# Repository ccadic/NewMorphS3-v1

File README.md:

# NewMorphS3-v1
SMall S3 DEV Board with PSP Joystick
@sulfuroid

Hi all this is the NEW MorphS3 with ESP32S3 wroom chip.
You get a battery charger on board - Most of the GPIOS available
You have a 176x320 IPS ST7789 Display (compatible with TFT_eSPI 
There is a small PSP1000 joystick to help you make games
USB connection is a SMD USB C

Heve fun.

BOM and links to the components: https://github.com/ccadic/NewMorphS3-v1/blob/main/NewmorphS3-BOM.xlsx

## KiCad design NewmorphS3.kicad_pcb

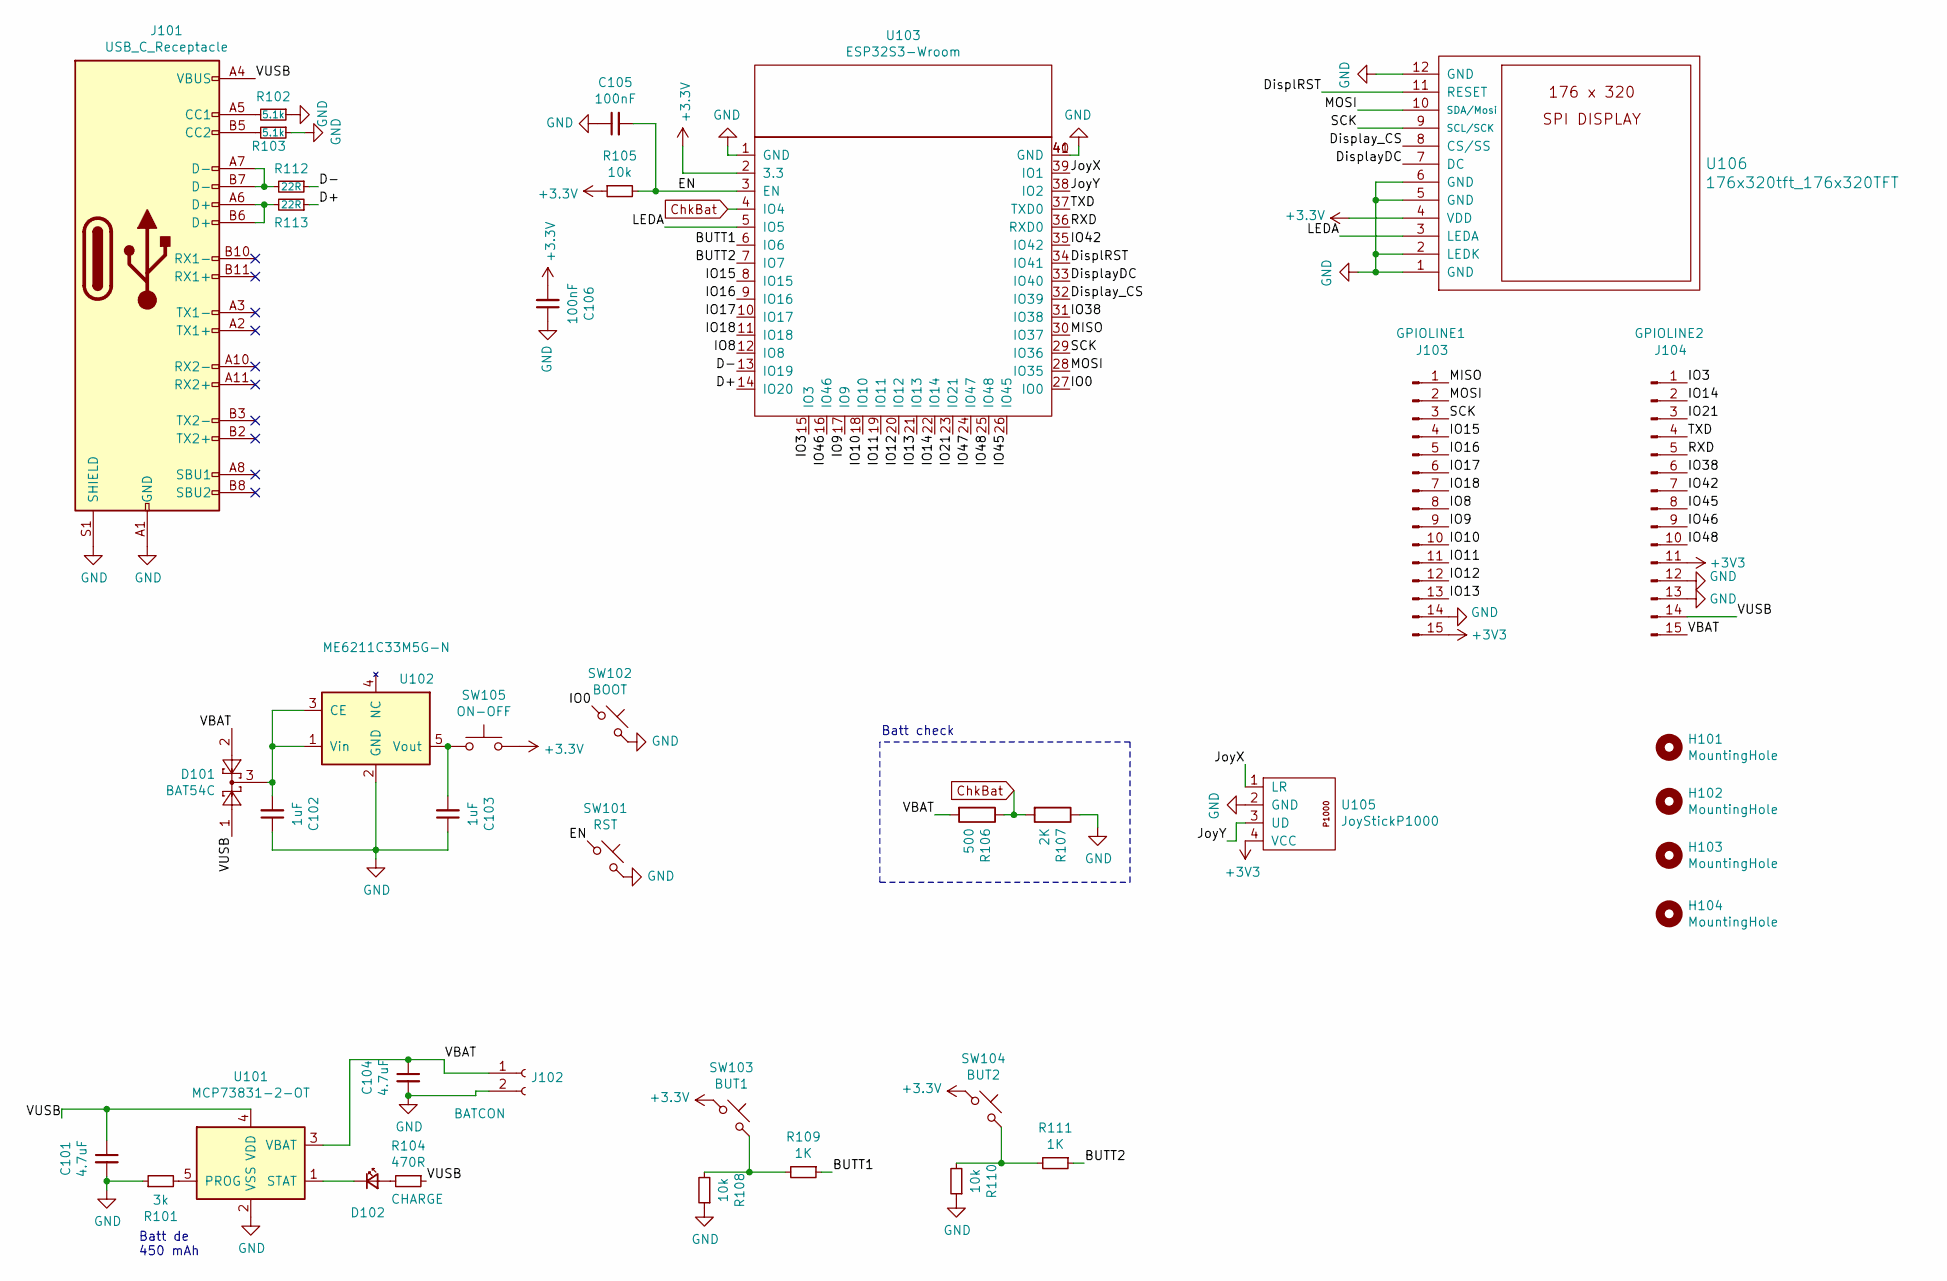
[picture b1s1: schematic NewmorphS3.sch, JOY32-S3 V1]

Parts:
C101, C104: 4.7uF; C_0603_1608Metric
C102, C103: 1uF; C_0603_1608Metric
C105: 100nF; C_0805_2012Metric_Pad1.18x1.45mm_HandSolder
C106: 100nF; C_0603_1608Metric
D101: BAT54C; SOT-23
D102: CHARGE; LED_0603_1608Metric
H101, H102, H103, H104: MountingHole; MountingHole_2.2mm_M2_Pad_Via
J101: USB_C_Receptacle; GT-USB-7010
J102: BATCON; JST_PH_S2B-PH-SM4-TB_1x02-1MP_P2.00mm_Horizontal
J103: GPIOLINE1; PinHeader_1x15_P2.54mm_Vertical
J104: GPIOLINE2; PinHeader_1x15_P2.54mm_Vertical
R101: 3k; R_0603_1608Metric
R102, R103: 5.1k; R_0603_1608Metric
R104: 470R; R_0603_1608Metric
R105: 10k; R_0805_2012Metric_Pad1.20x1.40mm_HandSolder
R106: 500; R_0603_1608Metric
R107: 2K; R_0603_1608Metric
R108, R110: 10k; R_0603_1608Metric
R109, R111: 1K; R_0603_1608Metric
R112, R113: 22R; R_0603_1608Metric
SW101: RST; SKRPABE010
SW102: BOOT; SKRPABE010
SW103: BUT1; SW_TP1003
SW104: BUT2; SW_TP1003
SW105: ON-OFF; SW_SPDT_PCM12
U101: MCP73831-2-OT; SOT-23-5
U102: ME6211C33M5G-N; SOT-23-5
U103: ESP32S3-Wroom; ESP32-S3-wrooom
U105: JoyStickP1000; JoystickP1000
U106: 176x320tft_176x320TFT; ST7789-176x320

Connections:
/BUTT1: R109.1, U103.6 (IO6)
/BUTT2: R111.1, U103.7 (IO7)
/D+: R113.1, U103.14 (IO20)
/D-: R112.1, U103.13 (IO19)
/DisplRST: U103.34 (IO41), U106.11 (RESET)
/DisplayDC: U103.33 (IO40), U106.7 (DC)
/Display_CS: U103.32 (IO39), U106.8 (CS/SS)
/EN: C105.2, R105.2, SW101.1, U103.3 (EN)
/IO0: SW102.1, U103.27 (IO0)
/IO3: J104.1, U103.15 (IO3)
/IO8: J103.8, U103.12 (IO8)
/IO9: J103.9, U103.17 (IO9)
/IO10: J103.10, U103.18 (IO10)
/IO11: J103.11, U103.19 (IO11)
/IO12: J103.12, U103.20 (IO12)
/IO13: J103.13, U103.21 (IO13)
/IO14: J104.2, U103.22 (IO14)
/IO15: J103.4, U103.8 (IO15)
/IO16: J103.5, U103.9 (IO16)
/IO17: J103.6, U103.10 (IO17)
/IO18: J103.7, U103.11 (IO18)
/IO21: J104.3, U103.23 (IO21)
/IO38: J104.6, U103.31 (IO38)
/IO42: J104.7, U103.35 (IO42)
/IO45: J104.8, U103.26 (IO45)
/IO46: J104.9, U103.16 (IO46)
/IO48: J104.10, U103.25 (IO48)
/JoyX: U103.39 (IO1), U105.1 (LR)
/JoyY: U103.38 (IO2), U105.3 (UD)
/LEDA: U103.5 (IO5), U106.3 (LEDA)
/MISO: J103.1, U103.30 (IO37)
/MOSI: J103.2, U103.28 (IO35), U106.10 (SDA/Mosi)
/RXD: J104.5, U103.36 (RXD0)
/SCK: J103.3, U103.29 (IO36), U106.9 (SCL/SCK)
/TXD: J104.4, U103.37 (TXD0)
/VBAT: C104.1, D101.2, J102.1, J104.15, R106.2, U101.3 (VBAT)
/VUSB: C101.1, D101.1, J101.A4 (VBUS), J101.A9 (VBUS), J101.B4 (VBUS), J101.B9 (VBUS), J104.14, R104.1, U101.4 (VDD)
ChkBat: R106.1, R107.2, U103.4 (IO4)
GND: C101.2, C102.1, C103.1, C104.2, C105.1, C106.1, J101.A1 (GND), J101.A12 (GND), J101.B1 (GND), J101.B12 (GND), J101.S1 (SHIELD), J102.2, J103.14, J104.12, J104.13, R101.1, R102.1, R103.1, R107.1, R108.1, R110.1, SW101.2, SW102.2, U101.2 (VSS), U102.2 (GND), U103.1 (GND), U103.40 (GND), U103.41 (GND), U105.2 (GND), U106.1 (GND), U106.2 (LEDK), U106.5 (GND), U106.6 (GND), U106.12 (GND)
unnamed: C102.2, D101.3, U102.1 (Vin), U102.3 (CE)
unnamed: C103.2, SW105.1, U102.5 (Vout)
unnamed: D102.1 (K), U101.1 (STAT)
unnamed: D102.2 (A), R104.2
unnamed: J101.A5 (CC1), R102.2
unnamed: J101.A6 (D+), J101.B6 (D+), R113.2
unnamed: J101.A7 (D-), J101.B7 (D-), R112.2
unnamed: J101.B5 (CC2), R103.2
unnamed: R101.2, U101.5 (PROG)
unnamed: R108.2, R109.2, SW103.2
unnamed: R110.2, R111.2, SW104.2

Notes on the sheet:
Batt de 450 mAh
Batt check

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
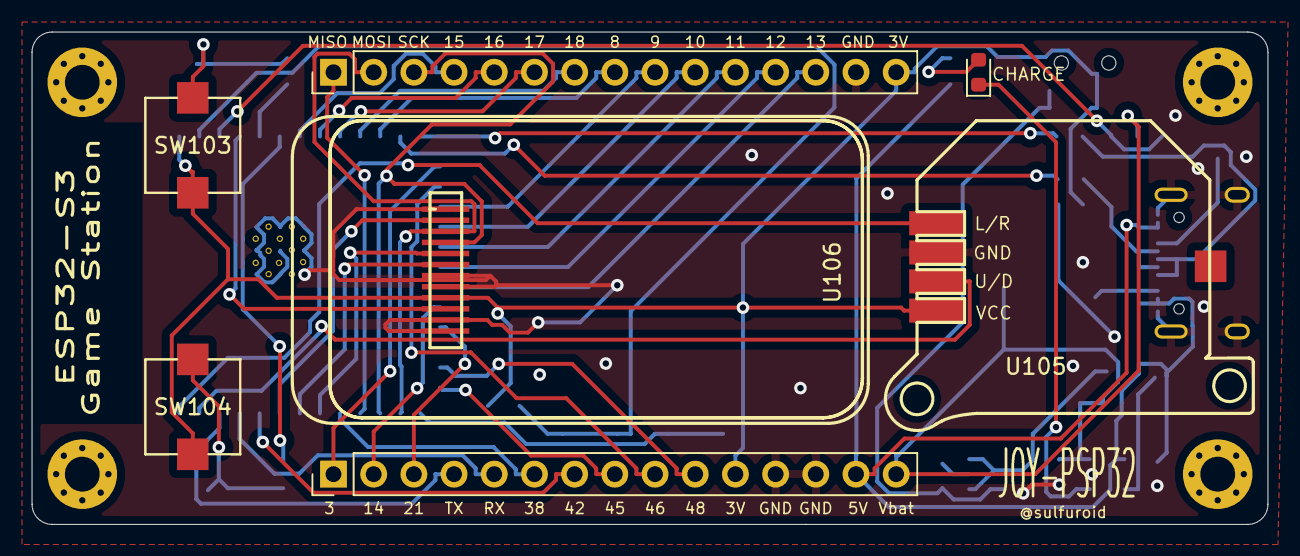
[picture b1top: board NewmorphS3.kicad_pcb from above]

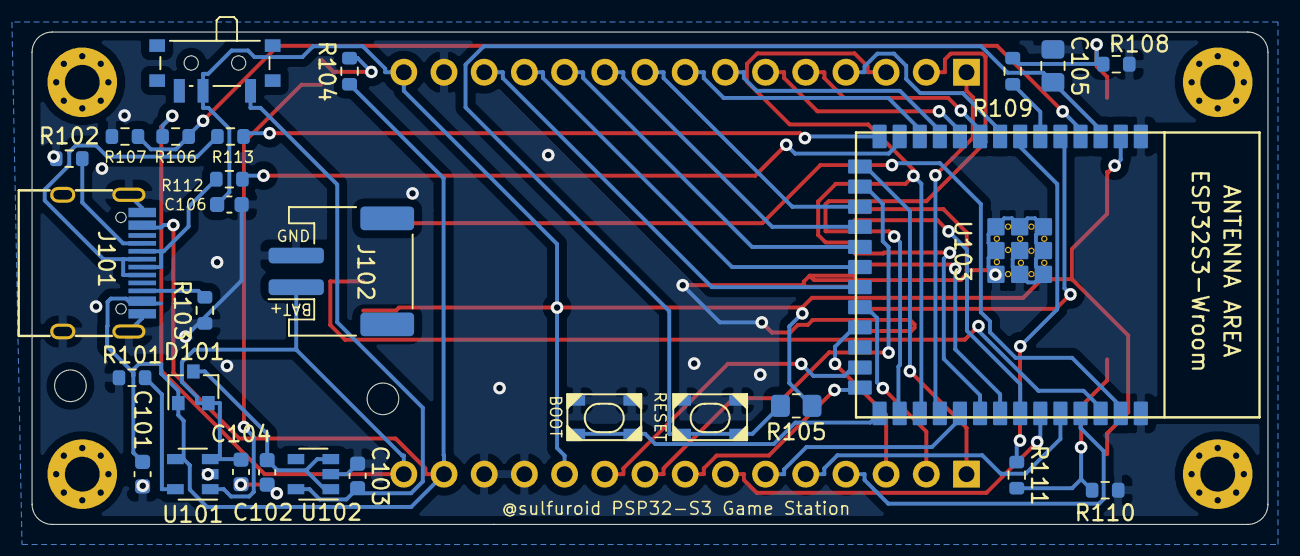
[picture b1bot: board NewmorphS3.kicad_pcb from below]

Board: 2 copper layers, 78.1 x 31.1 mm, 39 parts (28 on the bottom side), 51 nets.

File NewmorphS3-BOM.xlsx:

Comment,Designator,Footprint,LCSC
1uF | C102,C103 | Capacitor_SMD:C_0603_1608Metric
4.7uF | C101,C104 | Capacitor_SMD:C_0603_1608Metric
100nF | C105 | Capacitor_SMD:C_0805_2012Metric_Pad1.18x1.45mm_HandSolder
100nF | C106 | Capacitor_SMD:C_0603_1608Metric
BAT54C | D101 | Package_TO_SOT_SMD:SOT-23
CHARGE | D102 | LED_SMD:LED_0603_1608Metric
MountingHole | H101,H102,H103,H104 | MountingHole:MountingHole_2.2mm_M2_Pad_Via
USB_C_Receptacle | J101 | 27sharp:GT-USB-7010 |  | https://fr.aliexpress.com/item/1005001283294686.html
BATCON | J102 | Connector_JST:JST_PH_S2B-PH-SM4-TB_1x02-1MP_P2.00mm_Horizontal |  | https://fr.aliexpress.com/item/1005001664001210.html
GPIOLINE1 | J103 | Connector_PinHeader_2.54mm:PinHeader_1x15_P2.54mm_Vertical
GPIOLINE2 | J104 | Connector_PinHeader_2.54mm:PinHeader_1x15_P2.54mm_Vertical
3k | R101 | Resistor_SMD:R_0603_1608Metric
5.1k | R102,R103 | Resistor_SMD:R_0603_1608Metric
470R | R104 | Resistor_SMD:R_0603_1608Metric
10k | R105 | Resistor_SMD:R_0805_2012Metric_Pad1.20x1.40mm_HandSolder
500 R | R106 | Resistor_SMD:R_0603_1608Metric
2K | R107 | Resistor_SMD:R_0603_1608Metric
10k | R108,R110 | Resistor_SMD:R_0603_1608Metric
1K | R109,R111 | Resistor_SMD:R_0603_1608Metric
22R | R112,R113 | Resistor_SMD:R_0603_1608Metric
RST | SW101 | 27sharp:SKRPABE010 |  | https://fr.aliexpress.com/item/32728256843.html
BOOT | SW102 | 27sharp:SKRPABE010 |  | https://fr.aliexpress.com/item/32728256843.html
BUT1 | SW103 | 18650:SW_TP1003 |  | https://fr.aliexpress.com/item/32820232659.html
BUT2 | SW104 | 18650:SW_TP1003 |  | https://fr.aliexpress.com/item/32820232659.html
ON-OFF | SW105 | Button_Switch_SMD:SW_SPDT_PCM12 |  | https://fr.aliexpress.com/item/32770868105.html
MCP73831-2-OT | U101 | Package_TO_SOT_SMD:SOT-23-5
ME6211C33M5G-N | U102 | Package_TO_SOT_SMD:SOT-23-5
ESP32S3-Wroom | U103 | 27sharp:ESP32-S3-wrooom |  | https://fr.aliexpress.com/item/32901557709.html
JoyStickP1000 | U105 | 27sharp:JoystickP1000 |  | https://fr.aliexpress.com/item/1005004379601141.html
176x320tft_176x320TFT | U106 | 27sharp:ST7789-176x320 |  | https://fr.aliexpress.com/item/1005003099340799.html
